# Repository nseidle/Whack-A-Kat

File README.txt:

WAK-A-KAT was a project for Burning Man 2012. This is a reaction speed game based on the Wack-A-Mole game. 6 pipes stuck out of the ground about 3 feet tall. At the end of the two rows of pipes (three each) stood a gum ball dispenser. The dispenser was filled full of cat foot.

On the end of each pipe was a large carnival button. Buttons would randomly illuminate and the player would have to hit the button(s) as fast as they could. Throughout the night the game would average the scores together. If you had a score that was better than the average (less total time to complete the game), then you won! And the gum ball dispenser, modified with a continuous servo, would dispense an amount of dry cat food. Yum!

This project was one of the first where I used the Arduino Mega 2560. The PCB layout is a decent example of a shield design for the Mega.

I also used Bill Porter's MP3 library: http://www.billporter.info/sparkfun-mp3-shield-arduino-library/
You rock Bill!

Each pipe was wrapped in EL wire. This provided a level of safety but used quite a bit more power than I predicted causing the 12V battery to drain before the night was over. Lesson: measure your project's power usage before you assume a brick of a battery will do the job.

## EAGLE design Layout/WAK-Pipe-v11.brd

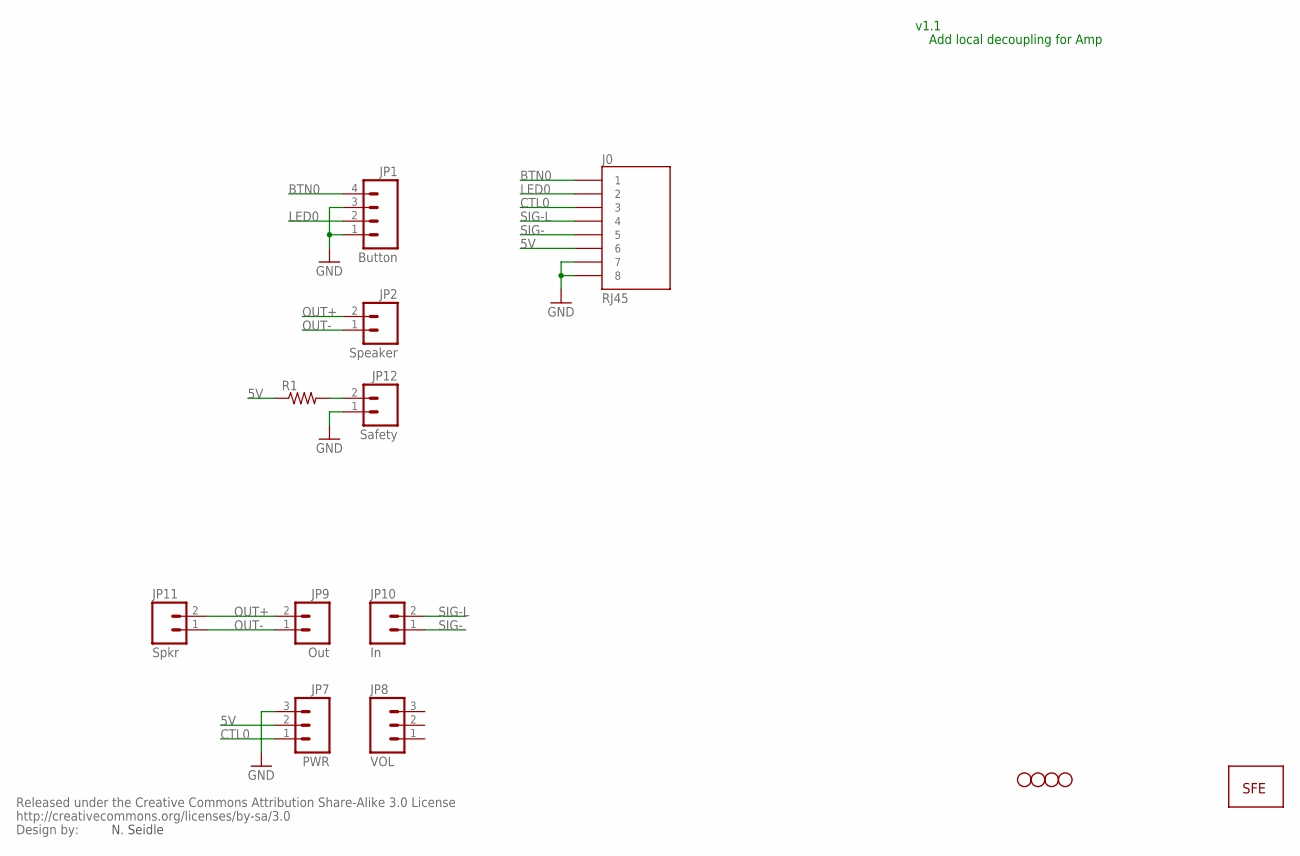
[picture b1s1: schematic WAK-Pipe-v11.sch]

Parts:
J0: RJ45; RJ45-8
JP1: Button; JST-4-PTH
JP2: Speaker; JST-2-PTH
JP3, JP4, JP5, JP6: STAND-OFF
JP7: PWR; 1X03
JP8: VOL; 1X03
JP9: Out; 1X02
JP10: In; 1X02
JP11: Spkr; 1X02
JP12: Safety; JST-2-PTH
R1: RESISTORAXIAL-0.3; AXIAL-0.3
U$1: LOGO-SFENEW; SFE-NEW-WEBLOGO
U$2: CREATIVE_COMMONS

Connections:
5V: J0.6, JP7.2, R1.P$1 (1)
BTN0: J0.1, JP1.4
CTL0: J0.3, JP7.1
GND: J0.7, J0.8, JP1.1, JP1.3, JP7.3, JP12.1
LED0: J0.2, JP1.2
unnamed: JP12.2, R1.P$2 (2)
OUT+: JP2.2, JP9.2, JP11.2
OUT-: JP2.1, JP9.1, JP11.1
SIG-: J0.5, JP10.1
SIG-L: J0.4, JP10.2

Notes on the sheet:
N. Seidle
v1.1
Add local decoupling for Amp

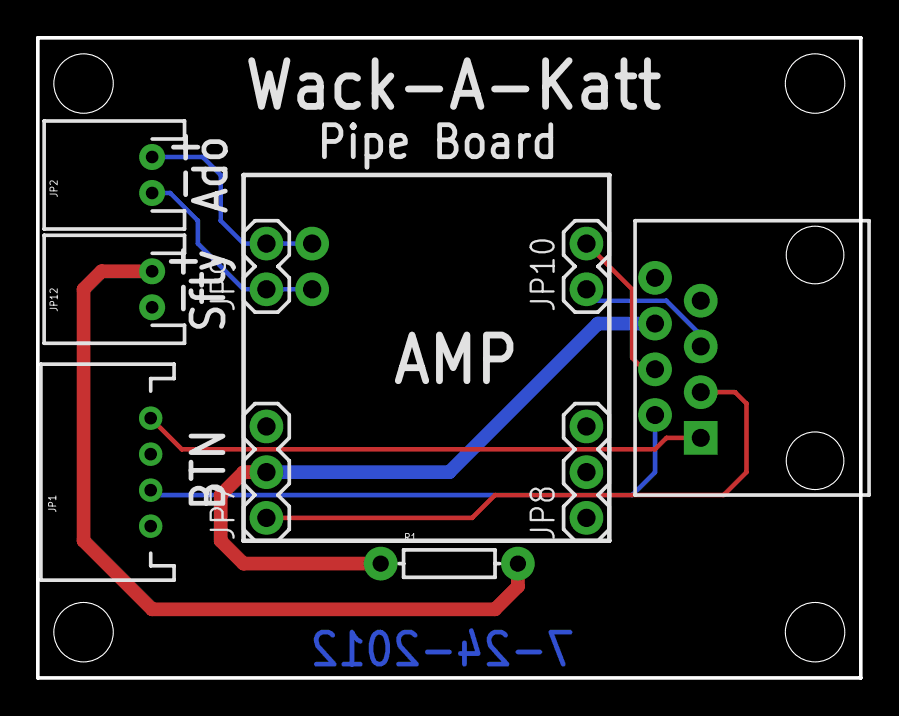
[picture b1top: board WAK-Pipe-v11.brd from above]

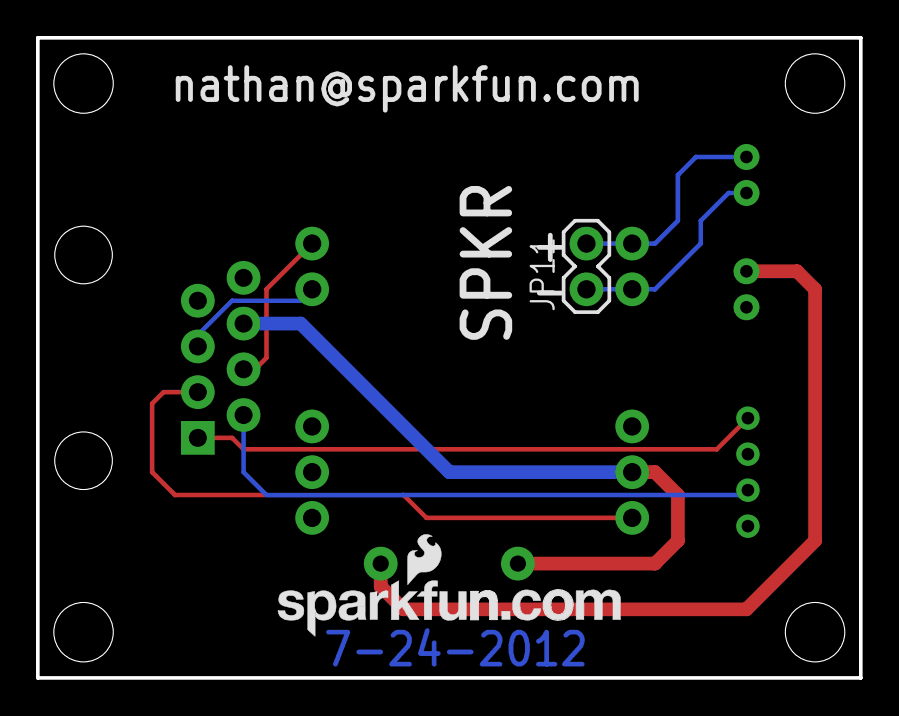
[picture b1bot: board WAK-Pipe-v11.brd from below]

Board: 2 copper layers, 45.7 x 35.6 mm, 16 parts (2 on the bottom side), 10 nets.

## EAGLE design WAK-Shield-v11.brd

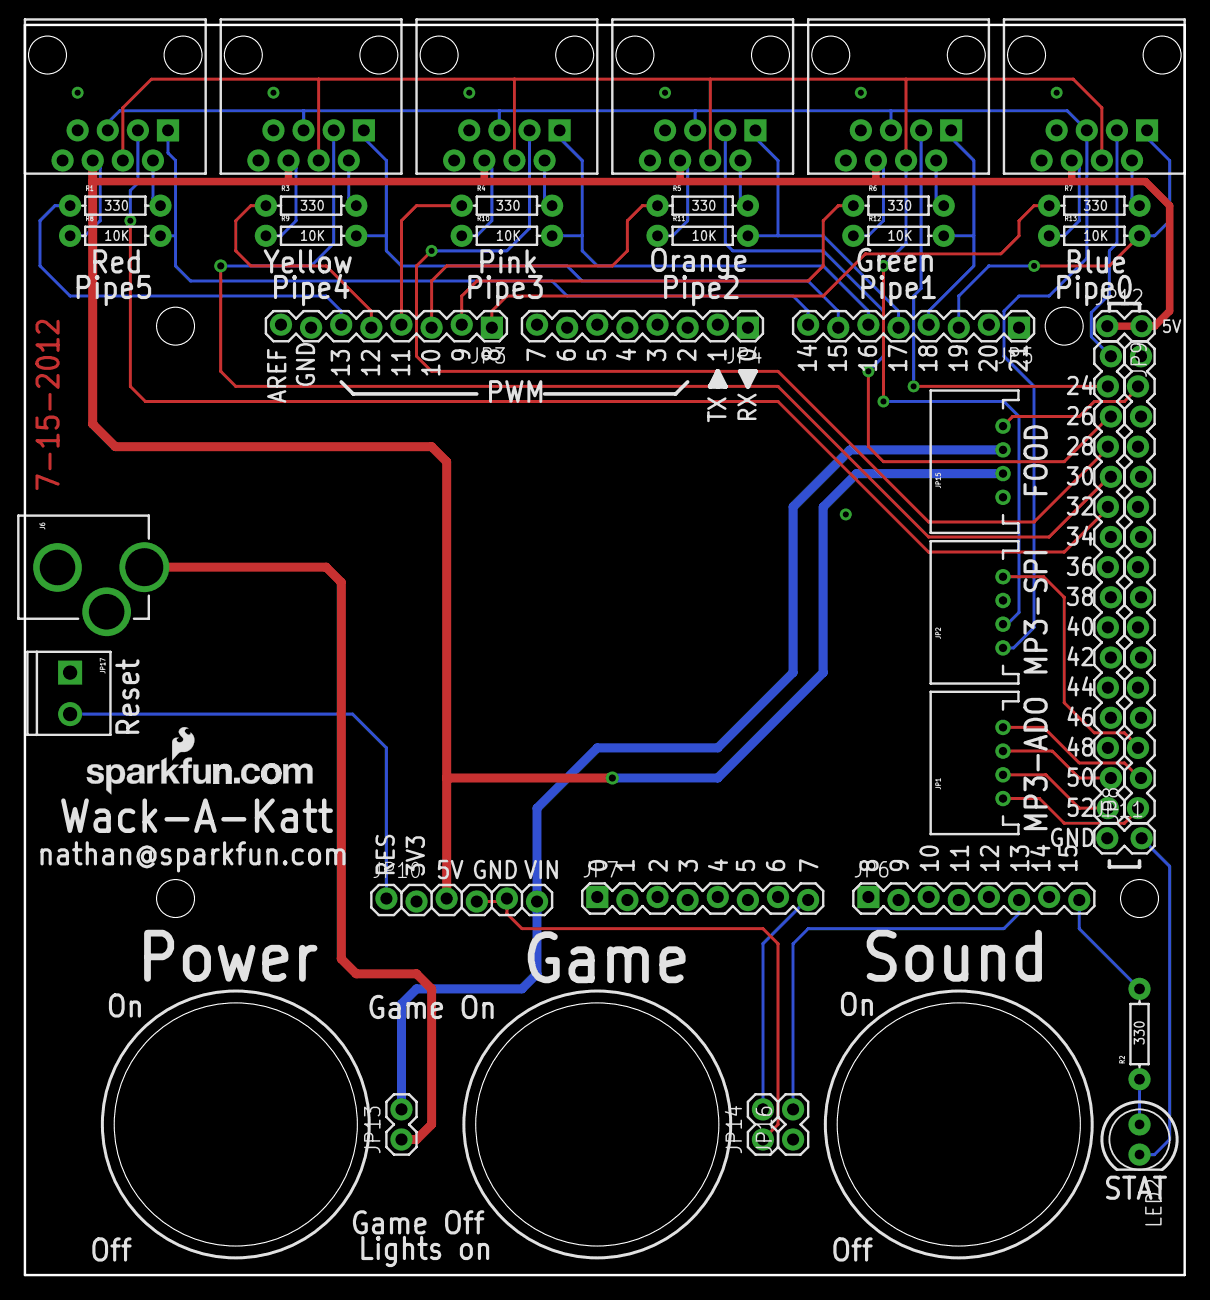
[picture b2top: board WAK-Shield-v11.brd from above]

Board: 2 copper layers, 97.8 x 105.4 mm, 40 parts (0 on the bottom side), 41 nets.

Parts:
J0, J1, J2, J3, J4, J5: RJ45; RJ45-8
J6: 12V; POWER_JACK_PTH_LOCK
JP1: MP3-SPI; JST-4-PTH
JP2: MP3-ADO; JST-4-PTH
JP3, JP4, JP5, JP6, JP7: 1X08_LOCK
JP8, JP9: M16LOCK; 1X16_LOCK
JP10: 1X06_LOCK
JP11, JP12: 1X02_LOCK
JP13: Power; 1X02
JP14: Game; 1X02
JP15: FOOD; JST-4-PTH
JP16: Audio; 1X02
JP17: Reset; SCREWTERMINAL-3.5MM-2
LED2: Green; LED5MM
R1, R2, R3, R4, R5, R6, R7: 330; AXIAL-0.3
R8, R9, R10, R11, R12, R13: 10K; AXIAL-0.3
U$1: LOGO-SFENEW; SFE-NEW-WEBLOGO
U$2: CREATIVE_COMMONS

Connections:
5V: J0.6, J1.6, J2.6, J3.6, J4.6, J5.6, JP10.3, JP12.1, JP12.2, JP15.2, R8.P$1, R9.P$1, R10.P$1, R11.P$1, R12.P$1, R13.P$1
A7: JP7.8, JP14.2
AUDIO-CTL: JP6.6, JP16.2
BTN0: J0.1, JP5.3, R13.P$2
BTN1: J1.1, JP5.4, R12.P$2
BTN2: J2.1, JP5.5, R11.P$2
BTN3: J3.1, JP5.6, R10.P$2
BTN4: J4.1, JP5.7, R9.P$2
BTN5: J5.1, JP5.8, R8.P$2
CTL0: J0.3, JP9.1
CTL1: J1.3, JP9.2
CTL2: J2.3, JP9.3
CTL3: J3.3, JP9.4
CTL4: J4.3, JP9.5
CTL5: J5.3, JP9.6
FOOD1: JP8.15, JP15.4
GND: J0.7, J0.8, J1.7, J1.8, J2.7, J2.8, J3.7, J3.8, J4.7, J4.8, J5.7, J5.8, J6.GND, J6.GNDBREAK, JP3.7, JP10.4, JP10.5, JP11.1, JP11.2, JP14.1, JP15.1, JP16.1, JP17.1, LED2.K
LED0: J0.2, R7.P$2
LED1: J1.2, R6.P$2
LED2: J2.2, R5.P$2
LED3: J3.2, R4.P$2
LED4: J4.2, R3.P$2
LED5: J5.2, R1.P$2
MISO: JP1.3, JP9.15
MOSI: JP1.4, JP8.2
MP3_RST: JP2.4, JP8.3
unnamed: JP3.6, R1.P$1
unnamed: JP3.5, R3.P$1
unnamed: JP3.4, R4.P$1
unnamed: JP3.3, R5.P$1
unnamed: JP3.2, R6.P$1
unnamed: JP3.1, R7.P$1
unnamed: J6.PWR, JP13.1
unnamed: LED2.A, R2.P$1
RES: JP10.1, JP17.2
SCLK: JP1.2, JP9.16
SD_CS: JP1.1, JP8.1
SIG-: J0.5, J1.5, J2.5, J3.5, J4.5, J5.5, JP2.1
SIG-L: J0.4, J1.4, J2.4, J3.4, J4.4, J5.4, JP2.2
STAT: JP6.8, R2.P$2
VIN: JP10.6, JP13.2, JP15.3

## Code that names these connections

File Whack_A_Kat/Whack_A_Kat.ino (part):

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
//Hardware connections
//-=-=-=-=-=-=-=-=-=-=-=-=-=-=-=-=-=-=-=-=-=-=-=-=-=-=-=-=-=-=
int led0 = 3;
int led1 = 5;
int led2 = 6;
int led3 = 9;
int led4 = 10;
int led5 = 11;

int button0 = A0;
int button1 = A1;
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
  randomSeed(A5);

  pinMode(led0, OUTPUT);
  pinMode(led1, OUTPUT);
  pinMode(led2, OUTPUT);
  pinMode(led3, OUTPUT);
  pinMode(led4, OUTPUT);
  pinMode(led5, OUTPUT);

  pinMode(button0, INPUT);
  pinMode(button1, INPUT);
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
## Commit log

2012-07-16 Original commit of firmware and some soudns.
2012-09-23 Last push before burning man
    This was the last update before burning man. Project worked well.
2012-10-22 Added Readme. Put files into directories.

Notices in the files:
Whack_A_Kat/Whack_A_Kat.ino:
This code is public domain but you buy me a beer if you use this and we meet someday (Beerware license).
parts and their libraries:
SparkFun: Released under the Creative Commons Attribution Share-Alike 3.0 License
SparkFun: http://creativecommons.org/licenses/by-sa/3.0
SparkFun-Connectors: Licensing: CC v3.0 Share-Alike You are welcome to use this library for commercial purposes.
